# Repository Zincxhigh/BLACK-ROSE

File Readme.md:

<p align=center>This Project is a Tribute to the increadible show called Mr. ROBOT</p>

## About

The Jammer is inspired by bluejammers work it works by injecting the firmware into the ESP32 and also has can charge with the TP4056 Module
The firmware allows the NFR antenna's to create a disturbance wave which distrurbs any type of radio wave wether it be wifi or bluetooth

## PCB design

The design was inspired by Mr. ROBOT and the design behind is WHITEROSE I intialy wanted to copy the design flow of blueJammer but then pivoted since it then wouldn't be
mine tho the system still follows the same principal to fit the firmware, The original had alot of aspect which is way better then mine and I would say that he made it more
convenient.

## CAD design

The design is bulky and atrocious but it was my second attempt at a Cad incasing so chill out and I know how bad everything fits but I Like the way it looks all techy 
so I will improve the design for better design but I will not change the bulky feeling as it stands out from those thin casings and also how else would I fit the Name
Elliot alderson if I don't have space.

The Antenna's are my Best work and it made me feel really smart of how went about fitting antenna's.

## Tribute 

Mr. ROBOT was one of those shows that makes you be more senseable in how you view the world in my prespective Elliot alderson is a hero of the slum and a victim of his
father's abuse his usage of drugs to ease the pain almost never works out and is shown multiple times yet he goes back to it he said he wasent addicted but he comes back anyway
at the end he faces the truth not bec he wanted but bec the enovirenement forced it to, This character is the definition of pure Cinema and I love it.

## Process

The whole thing is documented with Lapse and my struggles to build it.

https://lapse.hackclub.com/timelapse/RKgoAYn0gdhi
https://lapse.hackclub.com/timelapse/c7LD85HKvazp
https://lapse.hackclub.com/timelapse/GZly2jAn0SyG
https://lapse.hackclub.com/timelapse/8Luba1dF0wwt
https://lapse.hackclub.com/timelapse/mDnerefs9IRr
https://lapse.hackclub.com/timelapse/ZzycG_YzoOne
https://lapse.hackclub.com/timelapse/5GctGso8MU3v
https://lapse.hackclub.com/timelapse/K8lTaUW__fx5

## BOM

ESP32-RF DIY-PCB: This PCB can fit an ESP32-wroom-32U/E DevKitC and 2 nRF-modules, along with an 0.96" I2C OLED, LEDs and switches.
Remember: It is not intended for illegal use!
For this one, all you need is listed below:

Required:

[ESP32 Dev Module](https://www.aliexpress.com/item/1005006613312645.html?aff_fcid=7ec6c453e03e47f791e1678c5771be76-1793961471865-07212-_onYIVKr&tt=CPS_NORMAL&aff_fsk=_onYIVKr&aff_platform=shareComponent-detail&sk=_onYIVKr&aff_trace_key=7ec6c453e03e47f791e1678c5771be76-1793961471865-07212-_onYIVKr&terminal_id=f9433f24f032435b9e382b8b3f625bf6&afSmartRedirect=y) (Recommended: ESP32-32U CP2102, any ESP32 should work as long as it has the needed pins, 38P required!)
[nRF24L01+PA+LNA (2x)](https://www.aliexpress.com/item/1005007038556192.html?aff_fcid=5de9656f55384a399be70db537b09490-1793961555054-04715-_oma5UQx&tt=CPS_NORMAL&aff_fsk=_oma5UQx&aff_platform=shareComponent-detail&sk=_oma5UQx&aff_trace_key=5de9656f55384a399be70db537b09490-1793961555054-04715-_oma5UQx&terminal_id=f9433f24f032435b9e382b8b3f625bf6&afSmartRedirect=y)
[10-100uF Capacitor (2x)](https://www.aliexpress.com/item/1005002524973878.html?aff_fcid=685913518df2482ebd5012ebd063c496-1793961584165-05330-_oFvFeYX&tt=CPS_NORMAL&aff_fsk=_oFvFeYX&aff_platform=shareComponent-detail&sk=_oFvFeYX&aff_trace_key=685913518df2482ebd5012ebd063c496-1793961584165-05330-_oFvFeYX&terminal_id=f9433f24f032435b9e382b8b3f625bf6&afSmartRedirect=y) (any voltage above 5V)
[0.96" OLED Display I2C](https://www.aliexpress.com/item/1005006700828250.html?aff_fcid=a986efb889bc494199cd5f82151d975c-1793961610670-04507-_oCdkjPX&tt=CPS_NORMAL&aff_fsk=_oCdkjPX&aff_platform=shareComponent-detail&sk=_oCdkjPX&aff_trace_key=a986efb889bc494199cd5f82151d975c-1793961610670-04507-_oCdkjPX&terminal_id=f9433f24f032435b9e382b8b3f625bf6&afSmartRedirect=y)
[Slide Switch (2x)](https://www.aliexpress.com/item/1005004402594340.html?aff_fcid=a6e0bf51c0d84fa6a6275c6dae7452cb-1793961629990-07832-_c4eQKm5D&tt=CPS_NORMAL&aff_fsk=_c4eQKm5D&aff_platform=shareComponent-detail&sk=_c4eQKm5D&aff_trace_key=a6e0bf51c0d84fa6a6275c6dae7452cb-1793961629990-07832-_c4eQKm5D&terminal_id=f9433f24f032435b9e382b8b3f625bf6&afSmartRedirect=y)
[LEDs: 3mm LED box](https://www.aliexpress.com/item/1005004543292837.html?aff_fcid=2ad85a6d1a264c419fcf93a48db1c6eb-1793961652512-08271-_c4dAH9sF&tt=CPS_NORMAL&aff_fsk=_c4dAH9sF&aff_platform=shareComponent-detail&sk=_c4dAH9sF&aff_trace_key=2ad85a6d1a264c419fcf93a48db1c6eb-1793961652512-08271-_c4dAH9sF&terminal_id=f9433f24f032435b9e382b8b3f625bf6&afSmartRedirect=y)
[Resistor kit](https://www.aliexpress.com/item/1005002364388450.html?aff_fcid=a6d7a041cf834c739d29717820f169e7-1793961680917-08025-_oCoJ7LO&tt=CPS_NORMAL&aff_fsk=_oCoJ7LO&aff_platform=shareComponent-detail&sk=_oCoJ7LO&aff_trace_key=a6d7a041cf834c739d29717820f169e7-1793961680917-08025-_oCoJ7LO&terminal_id=f9433f24f032435b9e382b8b3f625bf6&afSmartRedirect=y)

## Additional:

[TP4056 Charging Module (Micro-USB/Type-C)](https://www.aliexpress.com/item/1005011903177016.html?spm=a2g0o.productlist.main.1.25927b03AX15MR&algo_pvid=98bfcc08-5d2e-4fb3-a08d-f70a8dd02a52&pdp_ext_f=%7B%22order%22%3A%2230%22%2C%22spu_best_type%22%3A%22price%22%2C%22eval%22%3A%221%22%2C%22fromPage%22%3A%22search%22%7D&utparam-url=scene%3Asearch%7Cquery_from%3A%7Cx_object_id%3A1005011903177016%7C_p_origin_prod%3A)
[JST PH 2.0 Connector](https://www.aliexpress.com/item/32665588344.html?aff_fcid=b2b83f5e036140cd9e04a603137ea045-1793961761739-01549-_ooSOhDd&tt=CPS_NORMAL&aff_fsk=_ooSOhDd&aff_platform=shareComponent-detail&sk=_ooSOhDd&aff_trace_key=b2b83f5e036140cd9e04a603137ea045-1793961761739-01549-_ooSOhDd&terminal_id=f9433f24f032435b9e382b8b3f625bf6&afSmartRedirect=y)
[3.7V Li-Ion Battery](https://www.aliexpress.com/item/1005005739065266.html?spm=a2g0o.productlist.main.4.50ff3971CezIQU&aem_p4p_detail=202611060243231576742317027980000193746&algo_pvid=5a5dd219-bca3-46a7-aa50-4ba3bf587e2b&pdp_ext_f=%7B%22order%22%3A%22305%22%2C%22eval%22%3A%221%22%2C%22fromPage%22%3A%22search%22%7D&utparam-url=scene%3Asearch%7Cquery_from%3A%7Cx_object_id%3A1005005739065266%7C_p_origin_prod%3A&search_p4p_id=202611060243231576742317027980000193746_1)
[3rd Antenna: **IPEX to SMA-F pigtail](https://www.aliexpress.com/item/1005007039901040.html?aff_fcid=deaede1fcf40455fb344425aee921f82-1793961832664-09513-_oFDpn1V&tt=CPS_NORMAL&aff_fsk=_oFDpn1V&aff_platform=shareComponent-detail&sk=_oFDpn1V&aff_trace_key=deaede1fcf40455fb344425aee921f82-1793961832664-09513-_oFDpn1V&terminal_id=f9433f24f032435b9e382b8b3f625bf6&afSmartRedirect=y)

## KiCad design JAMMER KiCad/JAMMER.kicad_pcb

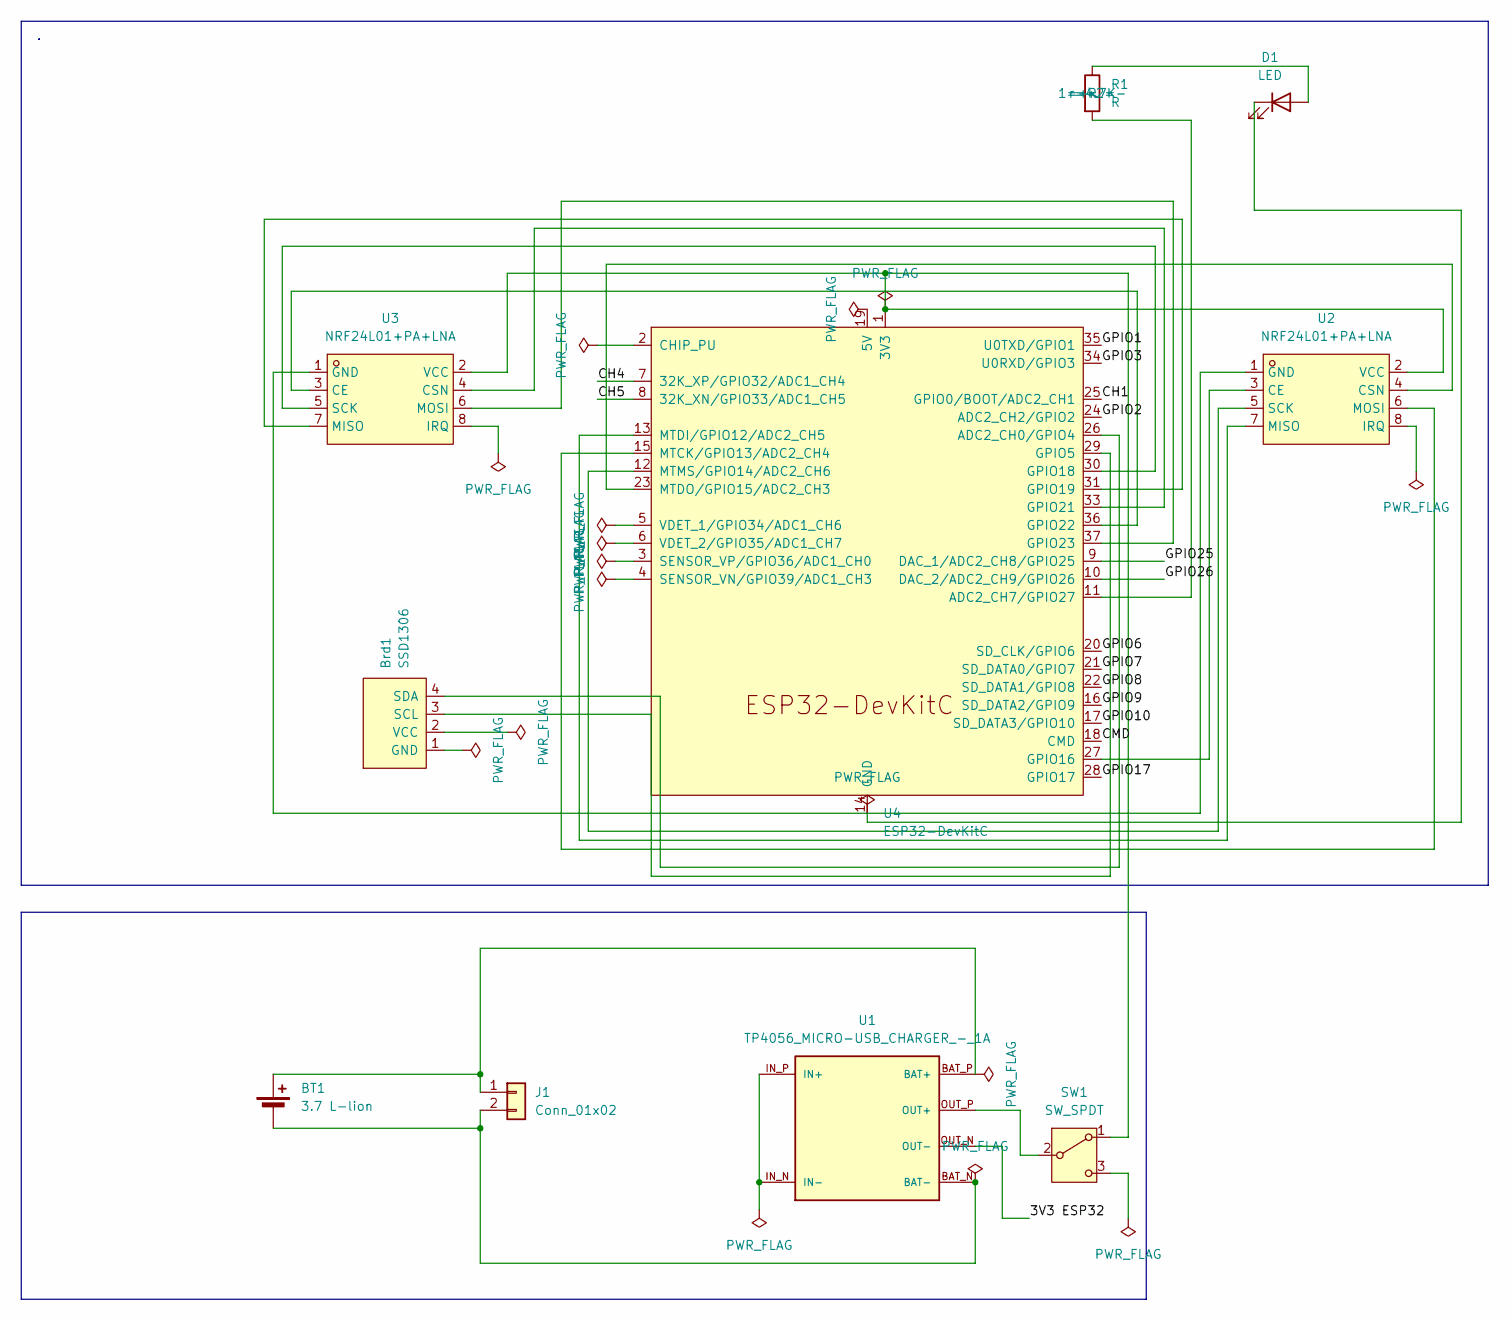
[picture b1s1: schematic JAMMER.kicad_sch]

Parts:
BT1: 3.7 L-lion; BatteryHolder_Bulgin_BX0036_1xC
Brd1: SSD1306; LCD_OLED_128X64_1.3_I2C
D1: LED; LED_D1.8mm_W1.8mm_H2.4mm_Horizontal_O1.27mm_Z1.6mm
J1: Conn_01x02; JWT_A3963_1x02_P3.96mm_Vertical
R1: R; R_0201_0603Metric
SW1: SW_SPDT; SW_1103M2S3CQE2
U1: TP4056_MICRO-USB_CHARGER_-_1A; MODULE_TP4056_MICRO-USB_CHARGER_-_1A
U2, U3: NRF24L01+PA+LNA; XCVR_NRF24L01P-MODULE-PCB; MPN nRF24L01+PA+LNA; LCSC Part C9900187674
U4: ESP32-DevKitC

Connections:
/3V3 ESP32: U1.OUT_N (OUT-)
/CH1: U4.25 (GPIO0/BOOT/ADC2_CH1)
/CH4: U4.7 (32K_XP/GPIO32/ADC1_CH4)
/CH5: U4.8 (32K_XN/GPIO33/ADC1_CH5)
/CMD: U4.18 (CMD)
/GPIO1: U4.35 (U0TXD/GPIO1)
/GPIO2: U4.24 (ADC2_CH2/GPIO2)
/GPIO3: U4.34 (U0RXD/GPIO3)
/GPIO6: U4.20 (SD_CLK/GPIO6)
/GPIO7: U4.21 (SD_DATA0/GPIO7)
/GPIO8: U4.22 (SD_DATA1/GPIO8)
/GPIO9: U4.16 (SD_DATA2/GPIO9)
/GPIO10: U4.17 (SD_DATA3/GPIO10)
/GPIO17: U4.28 (GPIO17)
/GPIO25: U4.9 (DAC_1/ADC2_CH8/GPIO25)
/GPIO26: U4.10 (DAC_2/ADC2_CH9/GPIO26)
unnamed: BT1.1 (+), J1.1, U1.BAT_P (BAT+)
unnamed: BT1.2 (-), J1.2, U1.BAT_N (BAT-)
unnamed: Brd1.3 (SCL), U4.29 (GPIO5)
unnamed: Brd1.4 (SDA), U4.26 (ADC2_CH0/GPIO4)
unnamed: D1.2 (A), R1.1
unnamed: D1.1 (K), U4.14 (GND), U4.32 (GND), U4.38 (GND)
unnamed: SW1.1 (A), U2.2 (VCC), U3.2 (VCC), U4.1 (3V3)
unnamed: SW1.2 (B), U1.OUT_P (OUT+)
unnamed: U1.IN_N (IN-), U1.IN_P (IN+)
unnamed: U2.3 (CE), U4.27 (GPIO16)
unnamed: U2.4 (CSN), U4.23 (MTDO/GPIO15/ADC2_CH3)
unnamed: U2.1 (GND), U3.1 (GND)
unnamed: U2.7 (MISO), U4.13 (MTDI/GPIO12/ADC2_CH5)
unnamed: U2.6 (MOSI), U4.15 (MTCK/GPIO13/ADC2_CH4)
unnamed: U2.5 (SCK), U4.12 (MTMS/GPIO14/ADC2_CH6)
unnamed: U3.3 (CE), U4.36 (GPIO22)
unnamed: U3.4 (CSN), U4.33 (GPIO21)
unnamed: U3.7 (MISO), U4.31 (GPIO19)
unnamed: U3.6 (MOSI), U4.37 (GPIO23)
unnamed: U3.5 (SCK), U4.30 (GPIO18)
unnamed: R1.2, U4.11 (ADC2_CH7/GPIO27)

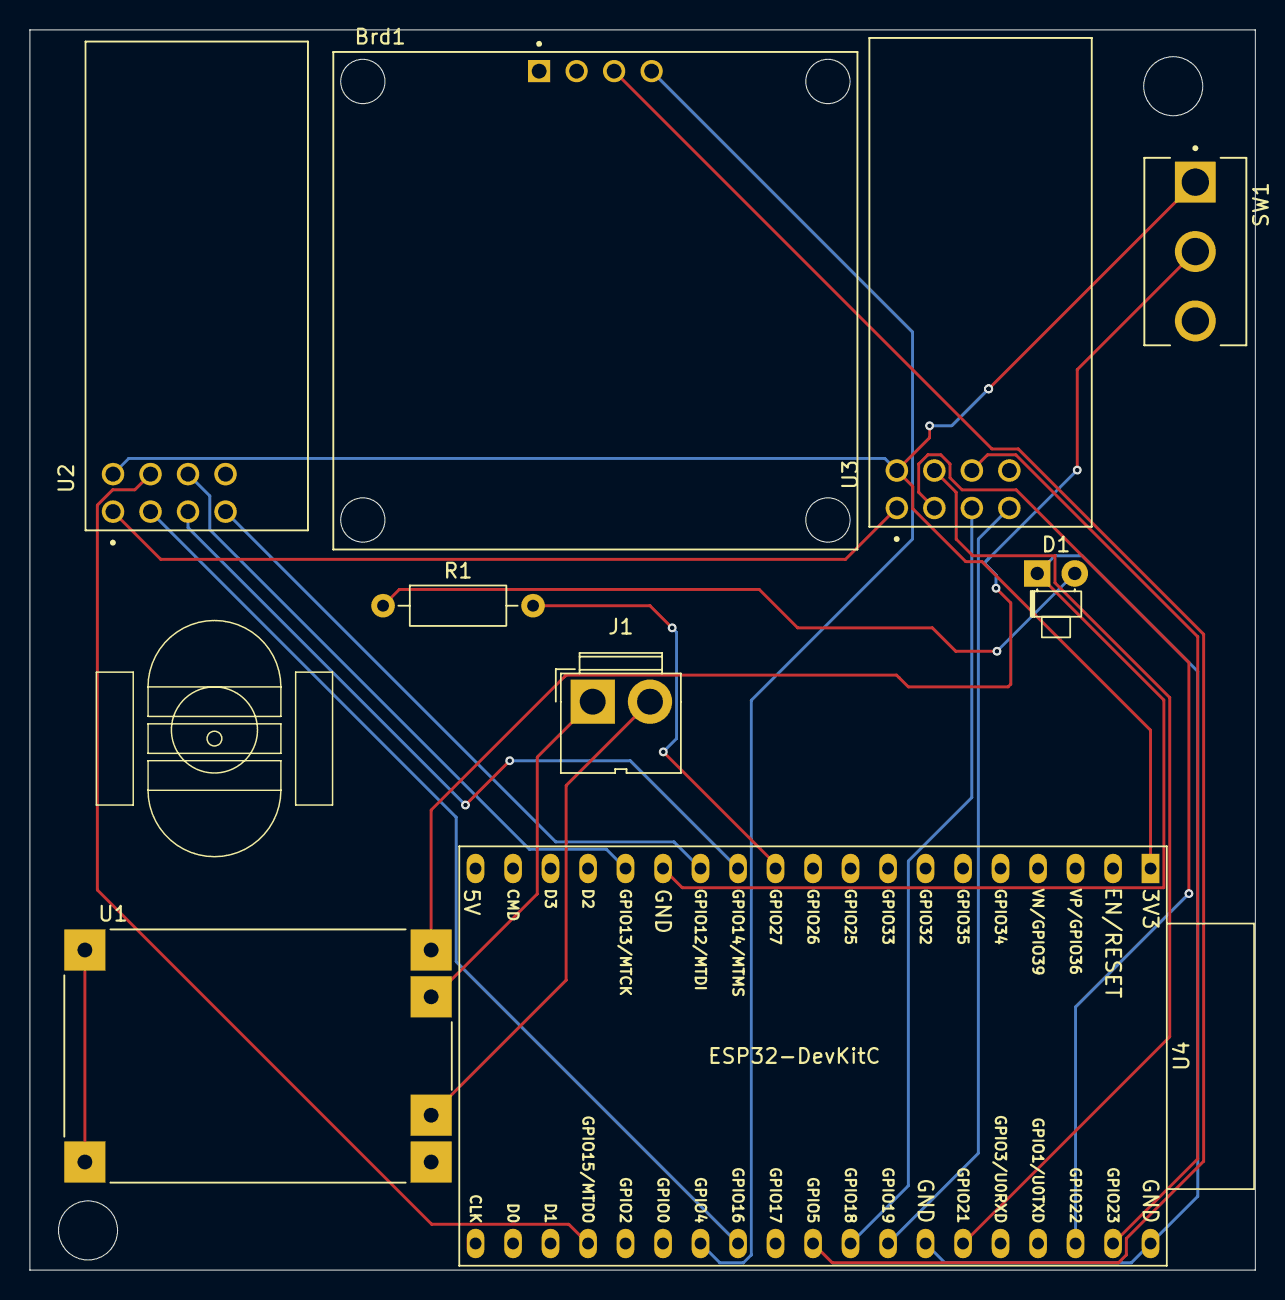
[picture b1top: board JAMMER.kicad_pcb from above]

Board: 2 copper layers, 83.0 x 84.0 mm, 9 parts (0 on the bottom side), 21 nets.
